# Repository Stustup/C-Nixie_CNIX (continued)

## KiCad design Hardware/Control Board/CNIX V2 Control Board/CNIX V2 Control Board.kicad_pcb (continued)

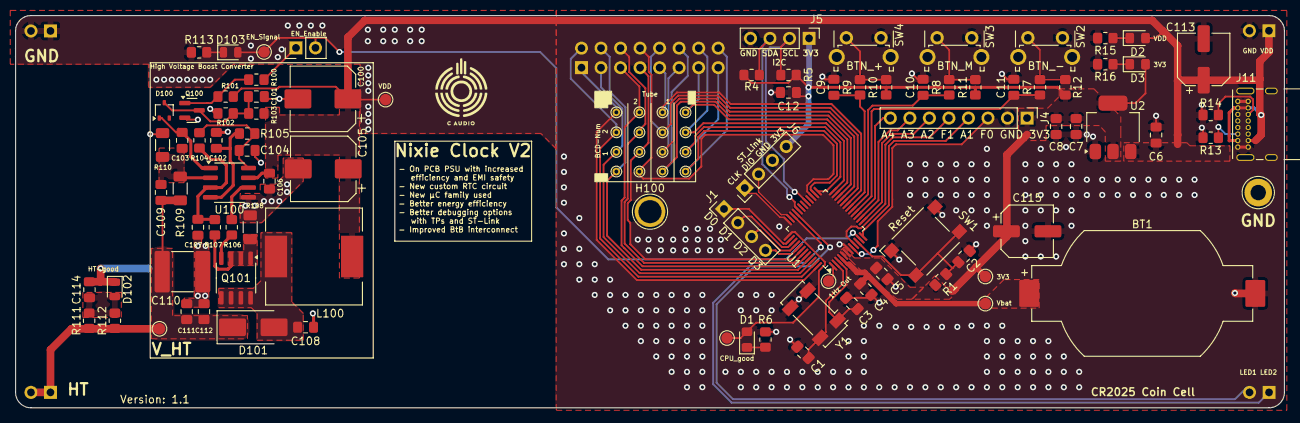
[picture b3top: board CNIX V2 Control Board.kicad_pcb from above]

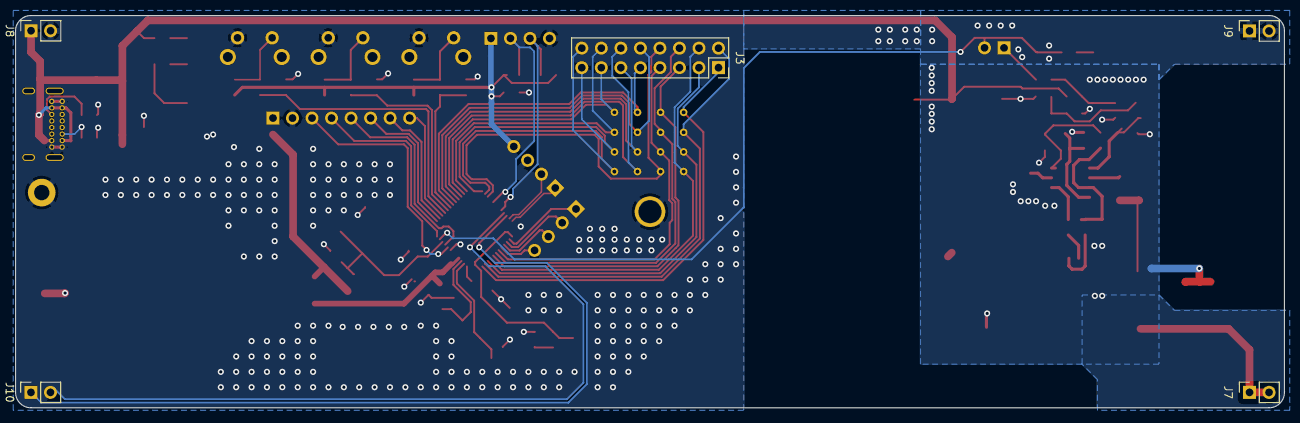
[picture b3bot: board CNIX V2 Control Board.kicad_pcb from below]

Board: 2 copper layers, 165.0 x 51.0 mm, 111 parts (5 on the bottom side), 68 nets.

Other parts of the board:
R6: 4k7; R_0805_2012Metric_Pad1.20x1.40mm_HandSolder

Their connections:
GND: R6.2; also elsewhere on the board
unnamed 52: R6.1; also elsewhere on the board

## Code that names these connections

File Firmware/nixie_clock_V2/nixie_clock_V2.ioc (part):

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Mcu.Name=STM32G051C(6-8)Tx
Mcu.Package=LQFP48
Mcu.UserName=STM32G051C8Tx
PA0.GPIOParameters=PinState,GPIO_PuPd,GPIO_Label
PA0.GPIO_Label=ht_EN
PA0.GPIO_PuPd=GPIO_PULLUP
PA0.PinState=GPIO_PIN_SET
PA0.Signal=GPIO_Output
PA1.GPIOParameters=PinState,GPIO_Label
PA1.GPIO_Label=addon_en
PA1.PinState=GPIO_PIN_SET
PA1.Signal=GPIO_Output
PA10.Mode=I2C
PA10.Signal=I2C1_SDA
PA11\ [PA9].GPIOParameters=GPIO_Label
PA11\ [PA9].GPIO_Label=led_sig_bot
PA11\ [PA9].Signal=GPIO_Output
PA12\ [PA10].GPIOParameters=GPIO_Label
PA12\ [PA10].GPIO_Label=led_sig_top
PA12\ [PA10].Signal=GPIO_Output
PA13.Mode=Serial_Wire
PA13.Signal=SYS_SWDIO
PA14-BOOT0.Mode=Serial_Wire
PA14-BOOT0.Signal=SYS_SWCLK
PA15.GPIOParameters=PinState,GPIO_Label
PA15.GPIO_Label=pwr_led
PA15.PinState=GPIO_PIN_SET
PA15.Signal=GPIO_Output
PA2.Signal=S_TIM2_CH3
PA5.GPIOParameters=GPIO_Label,GPIO_ModeDefaultEXTI
PA5.GPIO_Label=btn_minus
PA5.GPIO_ModeDefaultEXTI=GPIO_MODE_IT_FALLING
PA5.Signal=GPXTI5
PA6.GPIOParameters=GPIO_Label,GPIO_ModeDefaultEXTI
PA6.GPIO_Label=btn_menu
PA6.GPIO_ModeDefaultEXTI=GPIO_MODE_IT_FALLING
PA6.Signal=GPXTI6
PA7.GPIOParameters=GPIO_Label,GPIO_ModeDefaultEXTI
PA7.GPIO_Label=btn_plus
PA7.GPIO_ModeDefaultEXTI=GPIO_MODE_IT_FALLING
PA7.Signal=GPXTI7
PA9.Mode=I2C
PA9.Signal=I2C1_SCL
PB0.GPIOParameters=GPIO_Speed,PinState,GPIO_PuPd,GPIO_Label,GPIO_ModeDefaultOutputPP
PB0.GPIO_Label=co1_3
PB0.GPIO_ModeDefaultOutputPP=GPIO_MODE_OUTPUT_PP
PB0.GPIO_PuPd=GPIO_PULLDOWN
PB0.GPIO_Speed=GPIO_SPEED_FREQ_LOW
PB0.PinState=GPIO_PIN_RESET
PB0.Signal=GPIO_Output
PB1.GPIOParameters=GPIO_Speed,PinState,GPIO_PuPd,GPIO_Label,GPIO_ModeDefaultOutputPP
PB1.GPIO_Label=co1_2
PB1.GPIO_ModeDefaultOutputPP=GPIO_MODE_OUTPUT_PP
PB1.GPIO_PuPd=GPIO_PULLDOWN
PB1.GPIO_Speed=GPIO_SPEED_FREQ_LOW
PB1.PinState=GPIO_PIN_RESET
PB1.Signal=GPIO_Output
PB10.GPIOParameters=GPIO_Speed,PinState,GPIO_PuPd,GPIO_Label,GPIO_ModeDefaultOutputPP
PB10.GPIO_Label=co1_0
PB10.GPIO_ModeDefaultOutputPP=GPIO_MODE_OUTPUT_PP
PB10.GPIO_PuPd=GPIO_PULLDOWN
PB10.GPIO_Speed=GPIO_SPEED_FREQ_LOW
PB10.PinState=GPIO_PIN_RESET
PB10.Signal=GPIO_Output
PB11.GPIOParameters=GPIO_Speed,PinState,GPIO_PuPd,GPIO_Label,GPIO_ModeDefaultOutputPP
PB11.GPIO_Label=co0_3
PB11.GPIO_ModeDefaultOutputPP=GPIO_MODE_OUTPUT_PP
PB11.GPIO_PuPd=GPIO_PULLDOWN
PB11.GPIO_Speed=GPIO_SPEED_FREQ_LOW
PB11.PinState=GPIO_PIN_RESET
PB11.Signal=GPIO_Output
PB12.GPIOParameters=GPIO_Speed,PinState,GPIO_PuPd,GPIO_Label,GPIO_ModeDefaultOutputPP
PB12.GPIO_Label=co0_2
PB12.GPIO_ModeDefaultOutputPP=GPIO_MODE_OUTPUT_PP
PB12.GPIO_PuPd=GPIO_PULLDOWN
PB12.GPIO_Speed=GPIO_SPEED_FREQ_LOW
PB12.PinState=GPIO_PIN_RESET
PB12.Signal=GPIO_Output
PB13.GPIOParameters=GPIO_Speed,PinState,GPIO_PuPd,GPIO_Label,GPIO_ModeDefaultOutputPP
PB13.GPIO_Label=co0_1
PB13.GPIO_ModeDefaultOutputPP=GPIO_MODE_OUTPUT_PP
PB13.GPIO_PuPd=GPIO_PULLDOWN
PB13.GPIO_Speed=GPIO_SPEED_FREQ_LOW
PB13.PinState=GPIO_PIN_RESET
PB13.Signal=GPIO_Output
PB14.GPIOParameters=GPIO_Speed,PinState,GPIO_PuPd,GPIO_Label,GPIO_ModeDefaultOutputPP
PB14.GPIO_Label=co0_0
PB14.GPIO_ModeDefaultOutputPP=GPIO_MODE_OUTPUT_PP
PB14.GPIO_PuPd=GPIO_PULLDOWN
PB14.GPIO_Speed=GPIO_SPEED_FREQ_LOW
PB14.PinState=GPIO_PIN_RESET
PB14.Signal=GPIO_Output
PB15.GPIOParameters=GPIO_Speed,PinState,GPIO_PuPd,GPIO_Label,GPIO_ModeDefaultOutputPP
PB15.GPIO_Label=co2_0
PB15.GPIO_ModeDefaultOutputPP=GPIO_MODE_OUTPUT_PP
PB15.GPIO_PuPd=GPIO_PULLDOWN
PB15.GPIO_Speed=GPIO_SPEED_FREQ_LOW
PB15.PinState=GPIO_PIN_RESET
PB15.Signal=GPIO_Output
PB2.GPIOParameters=GPIO_Speed,PinState,GPIO_PuPd,GPIO_Label,GPIO_ModeDefaultOutputPP
PB2.GPIO_Label=co1_1
PB2.GPIO_ModeDefaultOutputPP=GPIO_MODE_OUTPUT_PP
PB2.GPIO_PuPd=GPIO_PULLDOWN
PB2.GPIO_Speed=GPIO_SPEED_FREQ_LOW
PB2.PinState=GPIO_PIN_RESET
PB2.Signal=GPIO_Output
PB3.GPIOParameters=GPIO_Speed,PinState,GPIO_PuPd,GPIO_Label,GPIO_ModeDefaultOutputPP
PB3.GPIO_Label=co2_1
PB3.GPIO_ModeDefaultOutputPP=GPIO_MODE_OUTPUT_PP
PB3.GPIO_PuPd=GPIO_PULLDOWN
PB3.GPIO_Speed=GPIO_SPEED_FREQ_LOW
PB3.PinState=GPIO_PIN_RESET
PB3.Signal=GPIO_Output
PB4.GPIOParameters=GPIO_Speed,PinState,GPIO_PuPd,GPIO_Label,GPIO_ModeDefaultOutputPP
PB4.GPIO_Label=co2_2
PB4.GPIO_ModeDefaultOutputPP=GPIO_MODE_OUTPUT_PP
PB4.GPIO_PuPd=GPIO_PULLDOWN
PB4.GPIO_Speed=GPIO_SPEED_FREQ_LOW
PB4.PinState=GPIO_PIN_RESET
PB4.Signal=GPIO_Output
PB5.GPIOParameters=GPIO_Speed,PinState,GPIO_PuPd,GPIO_Label,GPIO_ModeDefaultOutputPP
PB5.GPIO_Label=co2_3
PB5.GPIO_ModeDefaultOutputPP=GPIO_MODE_OUTPUT_PP
PB5.GPIO_PuPd=GPIO_PULLDOWN
PB5.GPIO_Speed=GPIO_SPEED_FREQ_LOW
PB5.PinState=GPIO_PIN_RESET
PB5.Signal=GPIO_Output
PB6.GPIOParameters=GPIO_Speed,PinState,GPIO_PuPd,GPIO_Label,GPIO_ModeDefaultOutputPP
PB6.GPIO_Label=co3_0
PB6.GPIO_ModeDefaultOutputPP=GPIO_MODE_OUTPUT_PP
PB6.GPIO_PuPd=GPIO_PULLDOWN
PB6.GPIO_Speed=GPIO_SPEED_FREQ_LOW
PB6.PinState=GPIO_PIN_RESET
PB6.Signal=GPIO_Output
PB7.GPIOParameters=GPIO_Speed,PinState,GPIO_PuPd,GPIO_Label,GPIO_ModeDefaultOutputPP
PB7.GPIO_Label=co3_1
PB7.GPIO_ModeDefaultOutputPP=GPIO_MODE_OUTPUT_PP
PB7.GPIO_PuPd=GPIO_PULLDOWN
PB7.GPIO_Speed=GPIO_SPEED_FREQ_LOW
PB7.PinState=GPIO_PIN_RESET
PB7.Signal=GPIO_Output
PB8.GPIOParameters=GPIO_Speed,PinState,GPIO_PuPd,GPIO_Label,GPIO_ModeDefaultOutputPP
PB8.GPIO_Label=co3_2
PB8.GPIO_ModeDefaultOutputPP=GPIO_MODE_OUTPUT_PP
PB8.GPIO_PuPd=GPIO_PULLDOWN
PB8.GPIO_Speed=GPIO_SPEED_FREQ_LOW
PB8.PinState=GPIO_PIN_RESET
PB8.Signal=GPIO_Output
PB9.GPIOParameters=GPIO_Speed,PinState,GPIO_PuPd,GPIO_Label,GPIO_ModeDefaultOutputPP
PB9.GPIO_Label=co3_3
PB9.GPIO_ModeDefaultOutputPP=GPIO_MODE_OUTPUT_PP
PB9.GPIO_PuPd=GPIO_PULLDOWN
PB9.GPIO_Speed=GPIO_SPEED_FREQ_LOW
PB9.PinState=GPIO_PIN_RESET
PB9.Signal=GPIO_Output
PC13.Mode=Calibration_1Hz
PC13.Signal=RTC_OUT1
PC14-OSC32_IN\ (PC14).Mode=LSE-External-Oscillator
PC14-OSC32_IN\ (PC14).Signal=RCC_OSC32_IN
PC15-OSC32_OUT\ (PC15).Mode=LSE-External-Oscillator
PC15-OSC32_OUT\ (PC15).Signal=RCC_OSC32_OUT
PD2.GPIOParameters=GPIO_PuPd,GPIO_Label
PD2.GPIO_Label=id_bit0
PD2.GPIO_PuPd=GPIO_PULLUP
PD2.Signal=GPIO_Input
PD3.GPIOParameters=GPIO_PuPd,GPIO_Label
PD3.GPIO_Label=id_bit1
PD3.GPIO_PuPd=GPIO_PULLUP
PD3.Signal=GPIO_Input
RCC.HSE_VALUE=8000000
RCC.SYSCLKFreq_VALUE=64000000
RCC.SYSCLKSource=RCC_SYSCLKSOURCE_PLLCLK
board=custom

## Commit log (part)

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2025-03-11 first commit, added boards
2025-03-11 pics
2025-04-03 added bom and populated board
2025-04-04 Added TODOS to README
2025-10-31 added firmware
2025-12-16 fixed stuff
2025-12-17 deleted firmware
2025-12-17 added new firmware
2025-12-17 added docs
2025-12-17 added bit masks for each tube
2025-12-17 added tube bit output
2025-12-17 fully added tube bit changing and display debug check
2025-12-17 fixed schematic
2025-12-17 fixed output caps and routung on pcb. Version Bump to 1.1
2025-12-17 found a bug, that the tubes are wired abckwards, needs to be fixed via new board
2025-12-17 added warning for tube fail
    https://www.mouser.de/ProductDetail/TDK/C5750X7T2E225K250KA?qs=vG%252BtRDh6KwCR7tEmlFz%2FKw%3D%3D
    exit
    quit
